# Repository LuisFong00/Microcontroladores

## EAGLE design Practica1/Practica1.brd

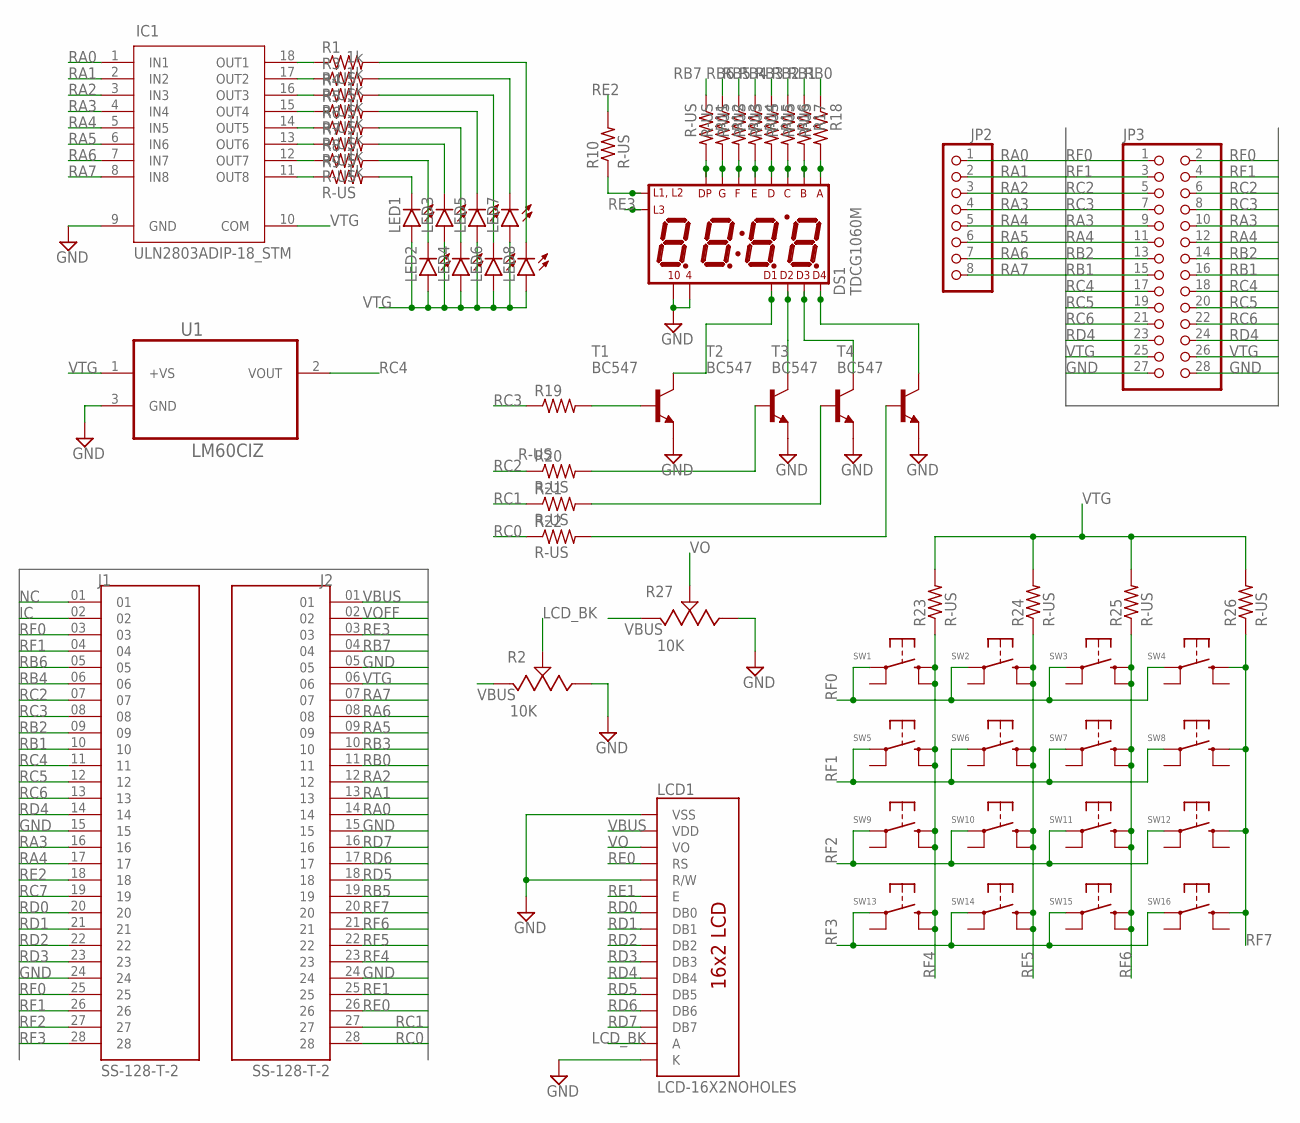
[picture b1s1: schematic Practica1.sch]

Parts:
DS1: TDCG1060M; DISPLAY_TDCG1060M
IC1: ULN2803ADIP-18_STM; DIP-18_STM
J1, J2: SS-128-T-2; SAMTEC_SS-128-T-2
JP2: PINHD-1X8BIG; 1X08-BIG
JP3: PINHD-2X14; 2X14
LCD1: LCD-16X2NOHOLES; LCD-16X2_NOHOLESNOSILK
LED1, LED2, LED3, LED4, LED5, LED6, LED7, LED8: LED3MM
R1, R3, R4, R5, R6, R7, R8, R9, R10, R11, R12, R13, R14, R15, R16, R17, R18, R19, R20, R21, R22, R23, R24, R25, R26: R-US; 0207/10
R2, R27: 10K; 3362P-1-103LF
SW1, SW2, SW3, SW4, SW5, SW6, SW7, SW8, SW9, SW10, SW11, SW12, SW13, SW14, SW15, SW16: 1825910-2; TE_1825910-2
T1, T2, T3, T4: BC547; TO92
U1: LM60CIZ; TO92/

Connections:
GND: DS1.4, DS1.10, IC1.9 (GND), J1.15, J1.24, J2.05, J2.15, J2.24, JP3.27, JP3.28, LCD1.1 (VSS), LCD1.5 (R/W), LCD1.16 (K), R2.3, R27.3, T1.1 (E), T2.1 (E), T3.1 (E), T4.1 (E), U1.3 (GND)
IC: J1.02
LCD_BK: LCD1.15 (A), R2.2
unnamed: IC1.18 (OUT1), R1.1
unnamed: IC1.17 (OUT2), R3.1
unnamed: IC1.16 (OUT3), R4.1
unnamed: IC1.15 (OUT4), R5.1
unnamed: IC1.14 (OUT5), R6.1
unnamed: IC1.13 (OUT6), R7.1
unnamed: IC1.12 (OUT7), R8.1
unnamed: IC1.11 (OUT8), R9.1
unnamed: DS1.12 (L1_L2), R10.1
unnamed: LED1.K (C), R9.2
unnamed: LED2.K (C), R8.2
unnamed: LED3.K (C), R7.2
unnamed: LED4.K (C), R6.2
unnamed: LED5.K (C), R5.2
unnamed: LED6.K (C), R4.2
unnamed: LED7.K (C), R3.2
unnamed: LED8.K (C), R1.2
unnamed: DS1.7 (DP), R11.2
unnamed: DS1.15 (G), R12.2
unnamed: DS1.11 (F), R13.2
unnamed: DS1.5 (E), R14.2
unnamed: DS1.3 (D), R15.2
unnamed: DS1.13 (C), R16.2
unnamed: DS1.16 (B), R17.2
unnamed: DS1.14 (A), R18.2
unnamed: DS1.8 (DIG4), T4.3 (C)
unnamed: DS1.6 (DIG3), T3.3 (C)
unnamed: DS1.2 (DIG2), T2.3 (C)
unnamed: DS1.1 (DIG1), T1.3 (C)
unnamed: R19.2, T1.2 (B)
unnamed: R20.2, T2.2 (B)
unnamed: R21.2, T3.2 (B)
unnamed: R22.2, T4.2 (B)
NC: J1.01
RA0: IC1.1 (IN1), J2.14, JP2.1
RA1: IC1.2 (IN2), J2.13, JP2.2
RA2: IC1.3 (IN3), J2.12, JP2.3
RA3: IC1.4 (IN4), J1.16, JP2.4, JP3.9, JP3.10
RA4: IC1.5 (IN5), J1.17, JP2.5, JP3.11, JP3.12
RA5: IC1.6 (IN6), J2.09, JP2.6
RA6: IC1.7 (IN7), J2.08, JP2.7
RA7: IC1.8 (IN8), J2.07, JP2.8
RB0: J2.11, R18.1
RB1: J1.10, JP3.15, JP3.16, R17.1
RB2: J1.09, JP3.13, JP3.14, R16.1
RB3: J2.10, R15.1
RB4: J1.06, R14.1
RB5: J2.19, R13.1
RB6: J1.05, R12.1
RB7: J2.04, R11.1
RC0: J2.28, R22.1
RC1: J2.27, R21.1
RC2: J1.07, JP3.5, JP3.6, R20.1
RC3: J1.08, JP3.7, JP3.8, R19.1
RC4: J1.11, JP3.17, JP3.18, U1.2 (VOUT)
RC5: J1.12, JP3.19, JP3.20
RC6: J1.13, JP3.21, JP3.22
RC7: J1.19
RD0: J1.20, LCD1.7 (DB0)
RD1: J1.21, LCD1.8 (DB1)
RD2: J1.22, LCD1.9 (DB2)
RD3: J1.23, LCD1.10 (DB3)
RD4: J1.14, JP3.23, JP3.24, LCD1.11 (DB4)
RD5: J2.18, LCD1.12 (DB5)
RD6: J2.17, LCD1.13 (DB6)
RD7: J2.16, LCD1.14 (DB7)
RE0: J2.26, LCD1.4 (RS)
RE1: J2.25, LCD1.6 (E)
RE2: J1.18, R10.2
RE3: DS1.9 (L3), J2.03
RF0: J1.03, J1.25, JP3.1, JP3.2, SW1.1, SW2.1, SW3.1, SW4.1
RF1: J1.04, J1.26, JP3.3, JP3.4, SW5.1, SW6.1, SW7.1, SW8.1
RF2: J1.27, SW9.1, SW10.1, SW11.1, SW12.1
RF3: J1.28, SW13.1, SW14.1, SW15.1, SW16.1
RF4: J2.23, R23.1, SW1.2 (S), SW1.4 (S1), SW5.2 (S), SW5.4 (S1), SW9.2 (S), SW9.4 (S1), SW13.2 (S), SW13.4 (S1)
RF5: J2.22, R24.1, SW2.2 (S), SW2.4 (S1), SW6.2 (S), SW6.4 (S1), SW10.2 (S), SW10.4 (S1), SW14.2 (S), SW14.4 (S1)
RF6: J2.21, R25.1, SW3.2 (S), SW3.4 (S1), SW7.2 (S), SW7.4 (S1), SW11.2 (S), SW11.4 (S1), SW15.2 (S), SW15.4 (S1)
RF7: J2.20, R26.1, SW4.2 (S), SW8.2 (S), SW12.2 (S), SW16.2 (S)
VBUS: J2.01, LCD1.2 (VDD), R2.1, R27.1
VO: LCD1.3 (VO), R27.2
VOFF: J2.02
VTG: IC1.10 (COM), J2.06, JP3.25, JP3.26, LED1.A, LED2.A, LED3.A, LED4.A, LED5.A, LED6.A, LED7.A, LED8.A, R23.2, R24.2, R25.2, R26.2, U1.1 (+VS)

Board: 2 copper layers, 63 parts (0 on the bottom side), 81 nets, no tracks yet.

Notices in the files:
parts and their libraries:
COPYRIGHT: Copyright (C) 2022 Ultra Librarian. All rights reserved.
